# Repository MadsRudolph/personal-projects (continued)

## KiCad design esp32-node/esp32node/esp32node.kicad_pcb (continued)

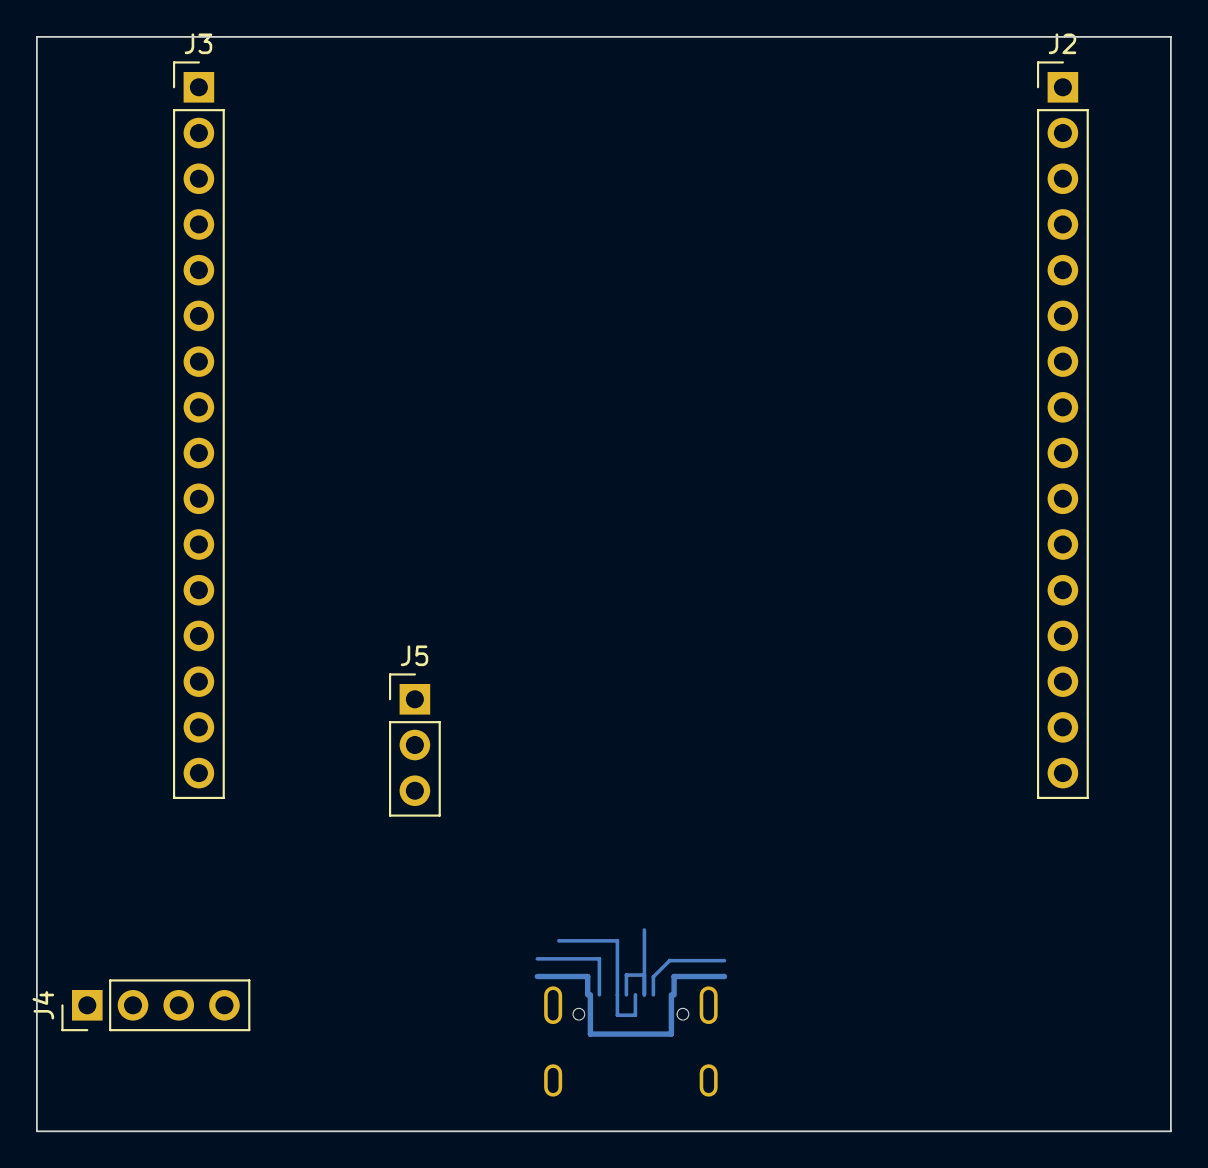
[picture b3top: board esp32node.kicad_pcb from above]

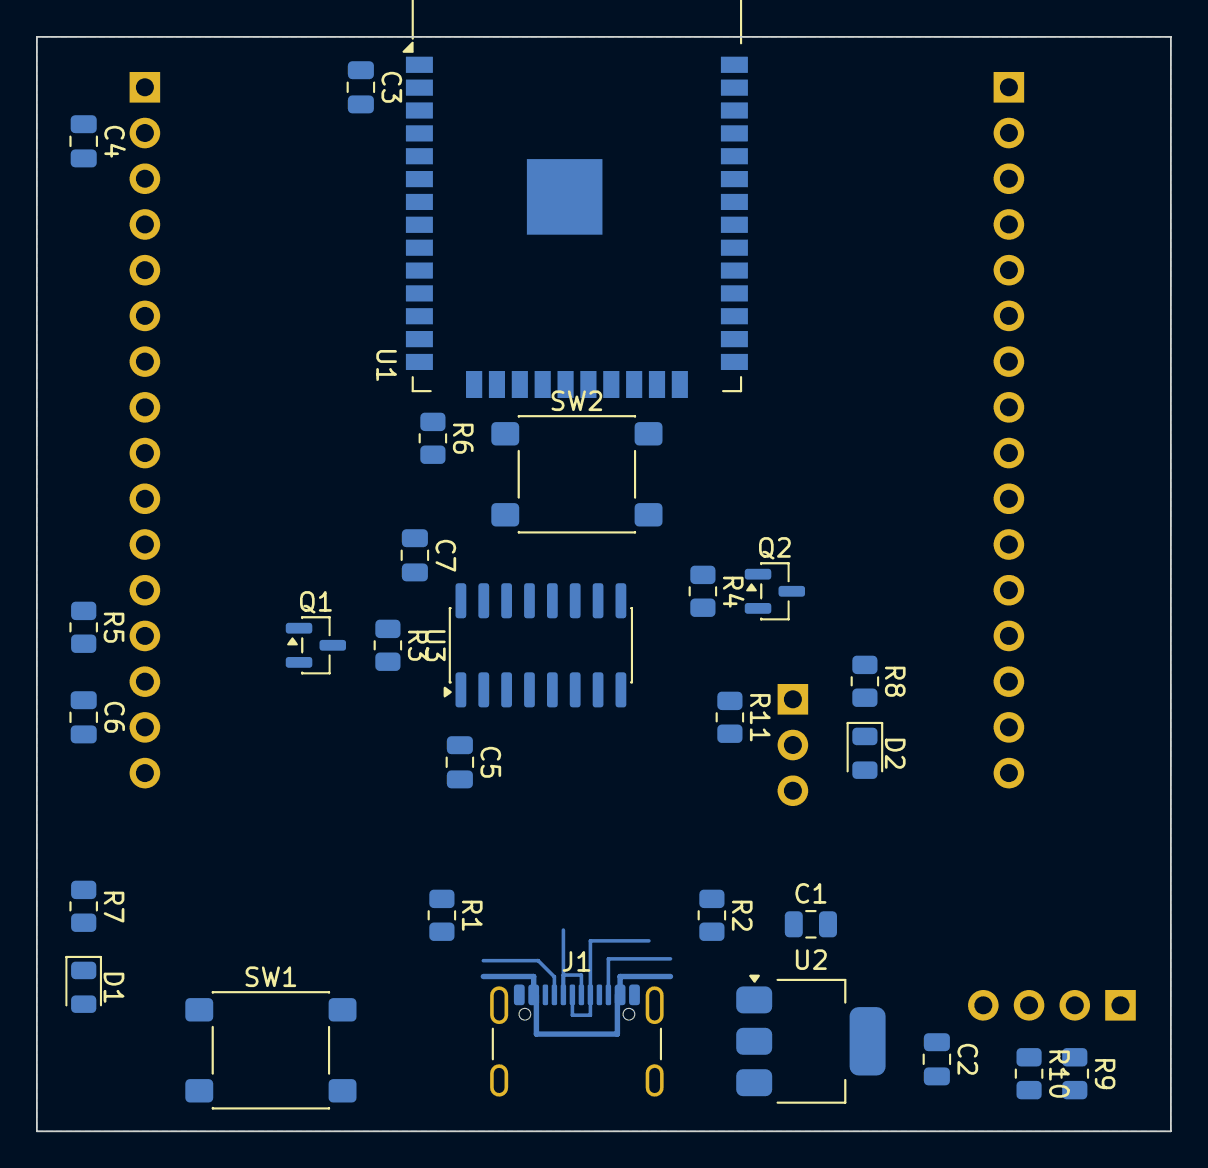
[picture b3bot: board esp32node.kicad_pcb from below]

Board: 2 copper layers, 63.0 x 60.8 mm, 32 parts (28 on the bottom side), 40 nets.

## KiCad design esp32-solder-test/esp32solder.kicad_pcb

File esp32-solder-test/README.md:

# ESP32 solder test board

This is the smallest board that proves an ESP32-WROOM-32 hand-soldered to copper etched on the
xTool F1 Ultra actually works. Once it's soldered, you flash it over a USB-UART adapter and blink the
LED on IO2. Everything except the module is through-hole and stocked at the DTU component shop.

- Single-sided, 54 x 46 mm, copper on the bottom (B.Cu). The ESP32 sits on the copper side and
  the through-hole parts go on top.
- Rule: 0.3 mm clearance / 0.5 mm track, inside what the test coupon proved (0.15 / 0.15 clean).
- Gates:
  - Schematic: `sch_score` PASS, ERC 0 violations, netlist verified.
  - Board: fully routed (11/11 nets, 0 unconnected, 0 vias, all tracks 0.5 mm), single GND pour
    in one piece, DRC clean on copper. The only leftovers are silkscreen cosmetics and one
    single-spoke thermal on SW2's GND pad, which is harmless.

## Bill of materials (DTU component shop part numbers)

| Ref | Part | Shop entry |
|---|---|---|
| U1 | ESP32-WROOM-32 module | not in the shop (bring your own) |
| U2 | LM317T, TO-220 | IC / Voltage Regulator / `LM317T` |
| R1 | 243 R | Resistor E96 `243R` |
| R2 | 392 R | Resistor E96 `392R` |
| R3, R4 | 10 k | Resistor E96 `10K0` |
| R5 | 332 R | Resistor E96 `332R` |
| R6 | 1 k | Resistor E96 `1K00` |
| C1, C2 | 10 uF electrolytic | Capacitor / Electrolytic `10µF` |
| C4 | 1 uF electrolytic | Capacitor / Electrolytic `1µF` |
| C3 | 100 nF ceramic | Capacitor / Ceramic `100n` |
| D1 | 3 mm LED, green (IO2) | LED `LED 3MM GRØN` |
| D2 | 3 mm LED, red (power) | LED `LED 3MM RØD` |
| SW1, SW2 | 6 mm tactile pushbutton | Hardware / Switch `Pushbutton` (check it has the 6.5 x 4.5 mm pin pattern) |
| J1 | 1x4 straight male header | Connector / Header `Header Male` (break off 4 pins) |

The shop has no fixed 3.3 V regulator, so the LM317 is set to 1.25 V x (1 + 392/243) = **3.27 V**.
R1 also draws the ~5 mA minimum load the LM317 needs. It needs about 1.7 V of headroom from 5 V,
which is plenty for flashing and blinking. WiFi does sag it: the factory AT firmware boot-looped
(see `BRINGUP.md`). The shop has no low-dropout 3.3 V part, so the fix for the next board is 7–9 V
into the LM317 plus 470 µF on 3V3. The recipe is in the kicad-laser-pcb skill's `references/esp32.md`.

## Laser files (`production/`)

Both files are **already mirrored to the copper side**, so do **not** mirror them in XCS.
Check: the copper text **"ESP32 TEST"** must read normally in the XCS preview.

1. **`esp32solder_copper_negative_MIRRORED.dxf`**: the copper to remove.
   - Import it, then **Make compound**. Black is removed; the pads, tracks and GND pour must be white.
   - Engrave with the **`Traces`** preset: 100 %, 600 mm/s, 10 passes, 240 lines/cm, one-way,
     30 kHz, cross hatch. See `../esp32-node/xtool/F1Ultra_PCB_presets.json`.
   - The drill holes are engraved as black dots in the pads, for centring.
2. **`esp32solder_drill_outline_MIRRORED.dxf`**: hole circles (layer `HOLES`) and board outline
   (layer `OUTLINE`).
   - Use the **`Cut/Drill`** vector preset (100 %, 100 mm/s, 160 passes). Both files share the
     same origin, so they stay registered if you import them into the same XCS canvas.
   - Hole sizes: 0.8 mm (resistors, caps), 0.9 mm (LEDs), 1.0 mm (header), 1.1 mm (LM317, buttons).

Sand lightly with 400 grit, then Framing, then Auto height adjustment, then Process.

## Soldering order

1. **ESP32 first**, while the board is still flat. It goes on the **copper side**, with the antenna
   overhanging the top edge, flush with the board edge. Tack two opposite corner pads, check
   alignment, then drag-solder the castellations. The big centre GND pad doesn't need solder;
   GND is carried by pins 1, 15 and 38.
2. Then the through-hole parts from the **plain side**, soldered on the copper side. Go lowest
   first: resistors, ceramic cap, LEDs (flat side = cathode), electrolytics (stripe = minus),
   buttons, header, and the LM317 last.
3. Before powering up, measure with a meter:
   - +5V to GND is not shorted.
   - Adjacent ESP32 pads are not bridged: probe neighbours, especially 1/2/3 (GND/3V3/EN) and
     34/35 (RXD0/TXD0).

## First power-up and flashing

- J1, starting at pin 1 (the square pad, nearest the antenna edge): **GND, 5V, TXD0 (ESP out), RXD0 (ESP in)**.
- Use a USB-UART adapter set to **3.3 V logic**. Wire adapter GND to GND, 5 V to 5V,
  adapter **RX to TXD0**, and adapter **TX to RXD0**.
- The red LED should light. Measure 3.2–3.3 V across C2.
- **Bootloader:** hold **BOOT**, tap **RESET**, release BOOT. Then run `esptool.py chip_id`
  (or `esptool.py flash_id`). If it answers, the module and all four UART/boot joints are good.
- Flash a blink sketch on **GPIO2** (Arduino `LED_BUILTIN` on the ESP32 Dev Module target) to see
  the green LED.

## Files

- `esp32solder_sch.py` builds `esp32solder.kicad_sch` (kicad-schematic DSL). It's the source of truth.
- `place_pcb.py` places the board (the footprint positions come from the flipped module's pads).
  The route came from FreeRouting 2.4.1 via `place_route.py`.
- `finish_pcb.py` adds the copper orientation text and refills the pour.
- `relink_pcb.py` links each footprint to its library and schematic symbol, so KiCad's
  schematic parity, cross-probing and "Update PCB from Schematic" work. `bootstrap_pcb.py`
  runs it automatically.
- `export_laser.py` writes the two DXFs above. It's the same negative-DXF approach as the coupon
  that came out perfectly.
- `esp32solder.placed.kicad_pcb` is the unrouted placement, kept for reference.
- `tools/pyshim` is a Python 3.14 workaround for pcbnew. Run the scripts with
  `PYTHONPATH=tools/pyshim python3 <script>`.

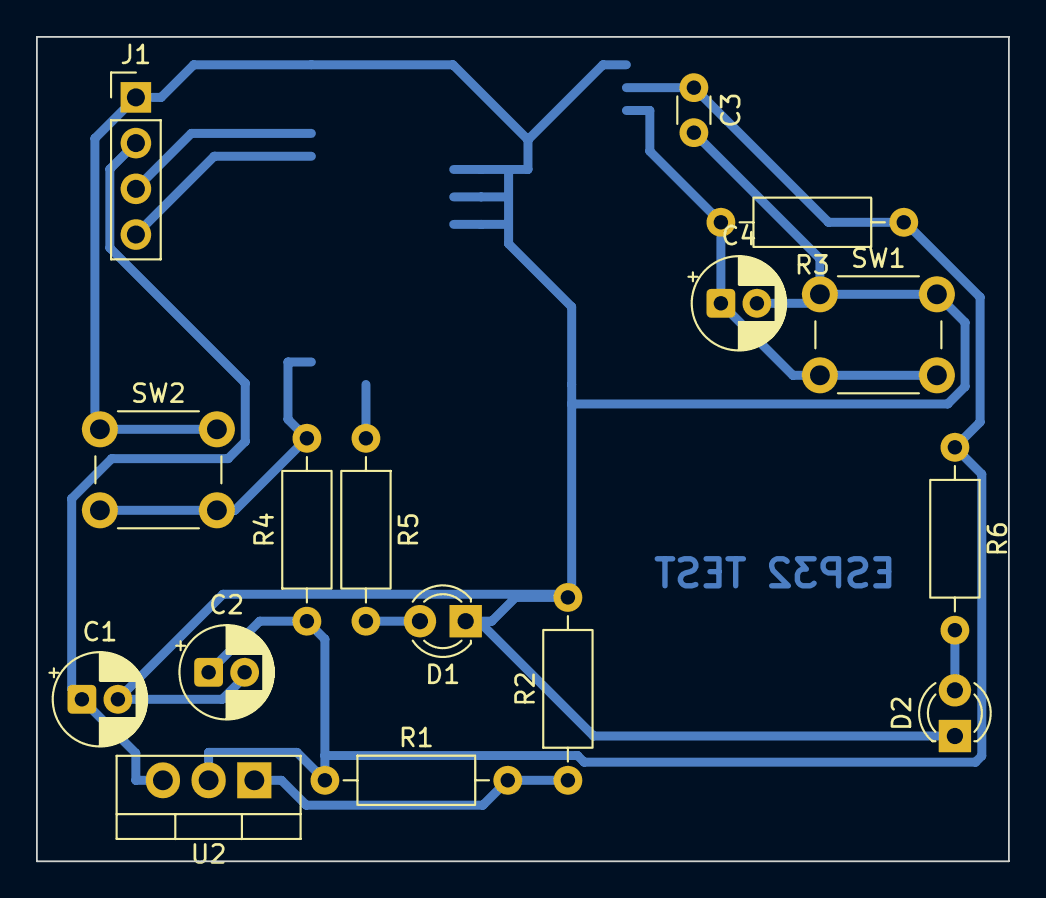
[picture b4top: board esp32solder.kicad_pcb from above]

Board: 2 copper layers, 54.0 x 45.8 mm, 17 parts (1 on the bottom side), 11 nets.

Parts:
C1, C2: 10u; CP_Radial_D5.0mm_P2.00mm
C3: 100n; C_Disc_D3.0mm_W1.6mm_P2.50mm
C4: 1u; CP_Radial_D5.0mm_P2.00mm
D1: LED green; LED_D3.0mm
D2: LED red; LED_D3.0mm
J1: UART / 5V; PinHeader_1x04_P2.54mm_Vertical
R1: 243; R_Axial_DIN0207_L6.3mm_D2.5mm_P10.16mm_Horizontal
R2: 392; R_Axial_DIN0207_L6.3mm_D2.5mm_P10.16mm_Horizontal
R3, R4: 10k; R_Axial_DIN0207_L6.3mm_D2.5mm_P10.16mm_Horizontal
R5: 332; R_Axial_DIN0207_L6.3mm_D2.5mm_P10.16mm_Horizontal
R6: 1k; R_Axial_DIN0207_L6.3mm_D2.5mm_P10.16mm_Horizontal
SW1: RESET; SW_PUSH_6mm
SW2: BOOT; SW_PUSH_6mm
U1: ESP32-WROOM-32; ESP32-WROOM-32_NoVias
U2: LM317T; TO-220-3_Vertical

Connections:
+3V3: C2.1, C3.1, R1.1, R3.1, R4.1, R6.1, U1.2, U2.2
/+5V_IN: C1.1, J1.2, U2.3
/IO0: R4.2, SW2.2, U1.25
/RXD0: J1.4, U1.34
/TXD0: J1.3, U1.35
GND: C1.2, C2.2, C3.2, C4.2, D1.1, D2.1, J1.1, R2.2, SW1.1, SW2.1, U1.1, U1.15, U1.38, U1.39
unnamed: D1.2, R5.2
unnamed: D2.2, R6.2
unnamed: C4.1, R3.2, SW1.2, U1.3
unnamed: R5.1, U1.24
unnamed: R1.2, R2.1, U2.1

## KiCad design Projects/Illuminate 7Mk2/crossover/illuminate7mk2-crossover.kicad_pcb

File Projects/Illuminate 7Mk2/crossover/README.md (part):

# Illuminate 7 Mk2 — crossover board

One passive crossover board per speaker, so **build two**. Single-sided,
through-hole only, CNC isolation-milled with an 0.8 mm end mill (the DTU 62768
process). The topology is the PrintYourSpeakers reference crossover, unchanged;
only the component **values** are substituted for what the DTU component shop
actually stocks.

| File | What it is |
|---|---|
| `illuminate7mk2-crossover.kicad_sch` / `.kicad_pro` | the schematic (KiCad 10) |
| `illuminate7mk2-crossover.pdf` / `.png` | rendered sheet |
| `illuminate7mk2-crossover-bom.csv` | BOM straight out of KiCad |
| `tools/crossover_layout.py` | the script that draws the sheet — edit this, not the `.kicad_sch` |
| `tools/make_coil_footprints.py` | generates the air-core coil footprints |
| `lib/crossover.pretty/` | those coil footprints |
| `sim/` | ngspice comparison of reference vs. substituted values |
| `illuminate7mk2-crossover.kicad_pcb` | the placed, unrouted board |
| `illuminate7mk2-crossover-pcb.png` | render of the placement |
| `tools/pcb_build.py` | builds and places the board from the netlist — re-run it after changing footprints |

Status: schematic done (ERC 0 violations), board routed by hand on B.Cu,
144.5 × 110 mm, four M4 corner holes, DRC clean. Mill and laser files are in
`production/illuminate7mk2-crossover/` (Gerbers + Excellon for the CAM,
`_silk_top.dxf` for the laser silkscreen). Coils: L102 may be a shop 270 µH if it passes
the LCR check; L101, L201 and L202 are to be wound.

## Circuit

```
IN+ ─┬─[ C 2u2 ∥ L 0.20mH ∥ R 9R4 ]─ A ─[ C 5u5 ]─ B ─[ C 10u1 ]─ TWEETER +
     │                                             └─[ L 0.25mH ]─┐
     │                                                            │
     └─[ C 41u ∥ L 0.70mH ∥ R 20R ]─ C ─[ L 2.0mH ]─ D ───────────┼─ WOOFER +
                                                    └─[ C 11u5 ]──┤
IN− ─────────────────────────────────────────────────────────────┴─ both −
```

The `GND` symbol on the sheet **is IN−**, the amplifier's negative speaker
terminal and the common return for both drivers. It is not chassis earth, and
the left and right boards' returns must stay separate — the Fosi V3 is a
bridged (BTL) class-D amp and its negative outputs are not ground.

## BOM

### From the DTU component shop — per board

| Qty | Shop part number | Refs | Replaces (design value) |
|----:|---|---|---|
| 2 | `2u2` film cap | C101, C103 | C101 = 2.0 µF tank; C103 is half of the 5.6 µF |
| 3 | `3u3` film cap | C102, C105, C207 | halves of 5.6 µF, 10 µF and 12 µF |
| 1 | `6u8` film cap | C104 | half of the 10 µF |
| 6 | `8u2` film cap | C201–C205, C206 | 5 in parallel = 40 µF tank; C206 is half of the 12 µF |
| 2 | `4R7 5W` power resistor | R101, R102 | in series = 9.4 Ω / 10 W (design 10 Ω) |
| 2 | `10R 5W` power resistor | R201, R202 | in series = 20 Ω / 10 W (design 20 Ω) |
| 3 | `2 pol skrueterminal` | J1, J2, J3 | input, tweeter, woofer |

**For two boards: double every quantity** — 4 × `2u2`, 6 × `3u3`, 2 × `6u8`,
12 × `8u2`, 4 × `4R7 5W`, 4 × `10R 5W`, 6 × 2-pole screw terminals.

How the parallel groups add up:

| Group | Shop parts | Result | Design value | Error |
|---|---|---|---|---|
| C101 | 2u2 | 2.2 µF | 2.0 µF | +10 % |
| C102 ∥ C103 | 3u3 + 2u2 | 5.5 µF | 5.6 µF | −1.8 % |
| C104 ∥ C105 | 6u8 + 3u3 | 10.1 µF | 10 µF | +1 % |
| C201…C205 | 5 × 8u2 | 41 µF | 40 µF | +2.5 % |
| C206 ∥ C207 | 8u2 + 3u3 | 11.5 µF | 12 µF | −4.2 % |
| R101 + R102 | 2 × 4R7 5W | 9.4 Ω / 10 W | 10 Ω / 10 W | −6 % |
| R201 + R202 | 2 × 10R 5W | 20 Ω / 10 W | 20 Ω / 10 W | exact |

### Coils — buy these, the shop has nothing usable

The shop stocks only small ferrite chokes with no current rating and a few bare
toroid cores, and no magnet wire. All four coils are **air-core, 0.8 mm
(20 AWG) wire**. Per board:

| Ref | Value | Target DCR | Dayton | Jantzen (Danish) |
|---|---|---|---|---|
| L101 | 0.20 mH | 0.29 Ω | AC20-20 | Air Core 0.20 mH / 0.80 mm |
| L102 | 0.25 mH | 0.35 Ω | AC20-25 | Air Core 0.25 mH / 0.80 mm |
| L201 | 0.70 mH | 0.60 Ω | AC20-70 | Air Core 0.70 mH / 0.80 mm |
| L202 | 2.0 mH | 1.06 Ω | AC202 | Air Core 2.0 mH / 0.80 mm |

Buy **eight** coils in total, two of each. Air-core only: an iron or ferrite
core saturates and distorts at woofer levels. Check the DCR on the datasheet —
it is part of the design, not a parasitic, and a coil with materially lower DCR
shifts the level of that branch.

### Or wind them yourself

Air-core coils are just wire on a bobbin, so with enamelled copper wire and an
LCR meter they can be wound at home. Use **0.8 mm** wire: it is what the Dayton
parts use, and it lands the DCR on the design value. Starting points (Wheeler
multilayer formula, 3D-printed bobbin, hand-wound with ~15 % slack):

| Ref | Value | Bobbin core Ø × width | Turns | Layers | OD | Wire | DCR |
|---|---|---|---|---|---|---|---|
| L101 | 0.20 mH | 20 × 10 mm | ~91 | 10 | ≈40 mm | 8.5 m | ≈0.29 Ω |
| L102 | 0.25 mH | 22 × 10 mm | ~96 | 10 | ≈42 mm | 9.6 m | ≈0.33 Ω |
| L201 | 0.70 mH | 28 × 12 mm | ~141 | 12 | ≈52 mm | 17.7 m | ≈0.60 Ω |
| L202 | 2.0 mH | 40 × 14 mm | ~195 | 14 | ≈68 mm | 33 m | ≈1.1 Ω |

Total wire for two boards: about 140 m of 0.8 mm. Procedure:

1. Print a bobbin with the core diameter above, flanges 2 mm taller than the
   expected winding depth, and a slot in one flange for the start lead.
2. Wind about 5 % fewer turns than the table, tight and in even layers, keeping
   the wire under tension. Count turns.
3. Measure L on the LCR meter at 1 kHz. Inductance goes with turns squared, so
   add turns as `N_new = N × sqrt(L_target / L_measured)`. Aim for ±3 %.
4. Measure DCR on the meter's DC-resistance range (or 4-wire if it has it) and
   compare with the target above. If the coil comes out *lower* than target,
   add a shop 5 W resistor in series to make up the difference (0.1–0.68 Ω are
   stocked); if it is more than ~0.1 Ω *higher*, the wire is thinner than
   0.8 mm or the coil is looser than assumed, and it is better to rewind.
5. Fix the winding with a few wraps of tape or a drop of glue, and keep the
   two coils of each branch at least one coil diameter apart, or at right
   angles, on the board so they do not couple.

Thicker wire (1.0 mm) gives about 30 % lower DCR than the design, so it needs
the series-resistor trim in step 4 on every coil; thinner wire (0.6 mm) makes
the DCR too high and should not be used for L202.

### Capacitor voltage ratings (read off the parts)

The Fosi V3 runs from 48 V and is bridged, so the input can swing about ±45 V.
The shop parts, as printed on them:

| Part | Rating | Verdict |
|---|---|---|
| 2u2 | 63 V | at the minimum; accepted, it is the weak point at full power |
| 3u3, 6u8 | 100 V | fine |
| 8u2 | 600 V | fine |

## Does this make an adequate crossover?

Yes. `sim/crossover_ac.cir` runs both versions side by side in ngspice with the
drivers modelled as plain resistors (4 Ω tweeter, 8 Ω woofer) and the coil DCRs
included, and `sim/compare.py` reports the difference over 100 Hz – 20 kHz:

| Branch | Max deviation from the reference | RMS |
|---|---|---|
| Tweeter | **+0.54 dB** at 12.7 kHz | 0.23 dB |
| Woofer | **+0.42 dB** at 1.05 kHz | 0.23 dB |

Nowhere in the band does either branch move more than 0.54 dB, and the woofer
stays under 0.5 dB everywhere. That is below the tolerance of the drivers
themselves (Dayton quotes ±10 % on Thiele-Small parameters, and 5 % film caps
are already worth a few tenths of a dB), and well under what is audible on a
broad, smooth deviation like this. The substituted set is fine.

Reproduce it with:

```bash
cd sim && ngspice -b crossover_ac.cir && python3 compare.py
```

## Board layout

`tools/pcb_build.py` builds the `.kicad_pcb` from the schematic netlist and
places it on a fixed floorplan that follows the signal flow, packed from the
footprints' real courtyards. **151 × 120 mm** on the measured
footprints, inside the mill's 203 × 152 mm envelope. Re-run after any footprint
change:

```bash
kicad-cli sch export netlist --format kicadsexpr -o /tmp/xo.net illuminate7mk2-crossover.kicad_sch
python3 ~/.claude/skills/kicad-laser-pcb/scripts/pcb_netlist_json.py /tmp/xo.net /tmp/xo.json
python3 tools/pcb_build.py /tmp/xo.json illuminate7mk2-crossover.kicad_pcb
```

```
 row A   L101 pads | C101 R101 R102 | C102 C103 | L102 pads | C104 C105 | J2 TWEETER   (top)
 row C   J1 IN, R201 R202 | C201 C202 C203 C204 C205 | L201 pads                     (middle)
 row B   L202 pads | C206 C207 | J3 WOOFER                                           (bottom)
```

- **The coils are not on the board.** They would not fit the mill envelope, so
  each coil has only its two lead pads (`crossover:L_OffBoard_P10.16mm`,
  10.16 mm pitch, 1.4 mm holes) at a board edge: L101 left edge top, L202 left
  edge bottom, L201 right edge middle, L102 top row between the tweeter caps.
  Mount the coil bodies overhanging the edge next to their pads, or glue them to
  the enclosure beside the board, and bring the leads to the pads. Keep any two
  coils at least one coil diameter apart, and never stack one on another.
- Input on the left edge, tweeter out top-right, woofer out bottom-right.
- Copper is **B.Cu only**, single-sided. A GND zone is defined on B.Cu (the
  return for both drivers) but not filled — fill it after routing.
- Design rules: 0.85 mm clearance, 1.0 mm minimum track, **2.0 mm default
  track**. Use 2 mm or wider for everything; this board carries amps.
- Four M4 holes in the corners, 6 mm in. The Illuminate enclosure has five M4
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
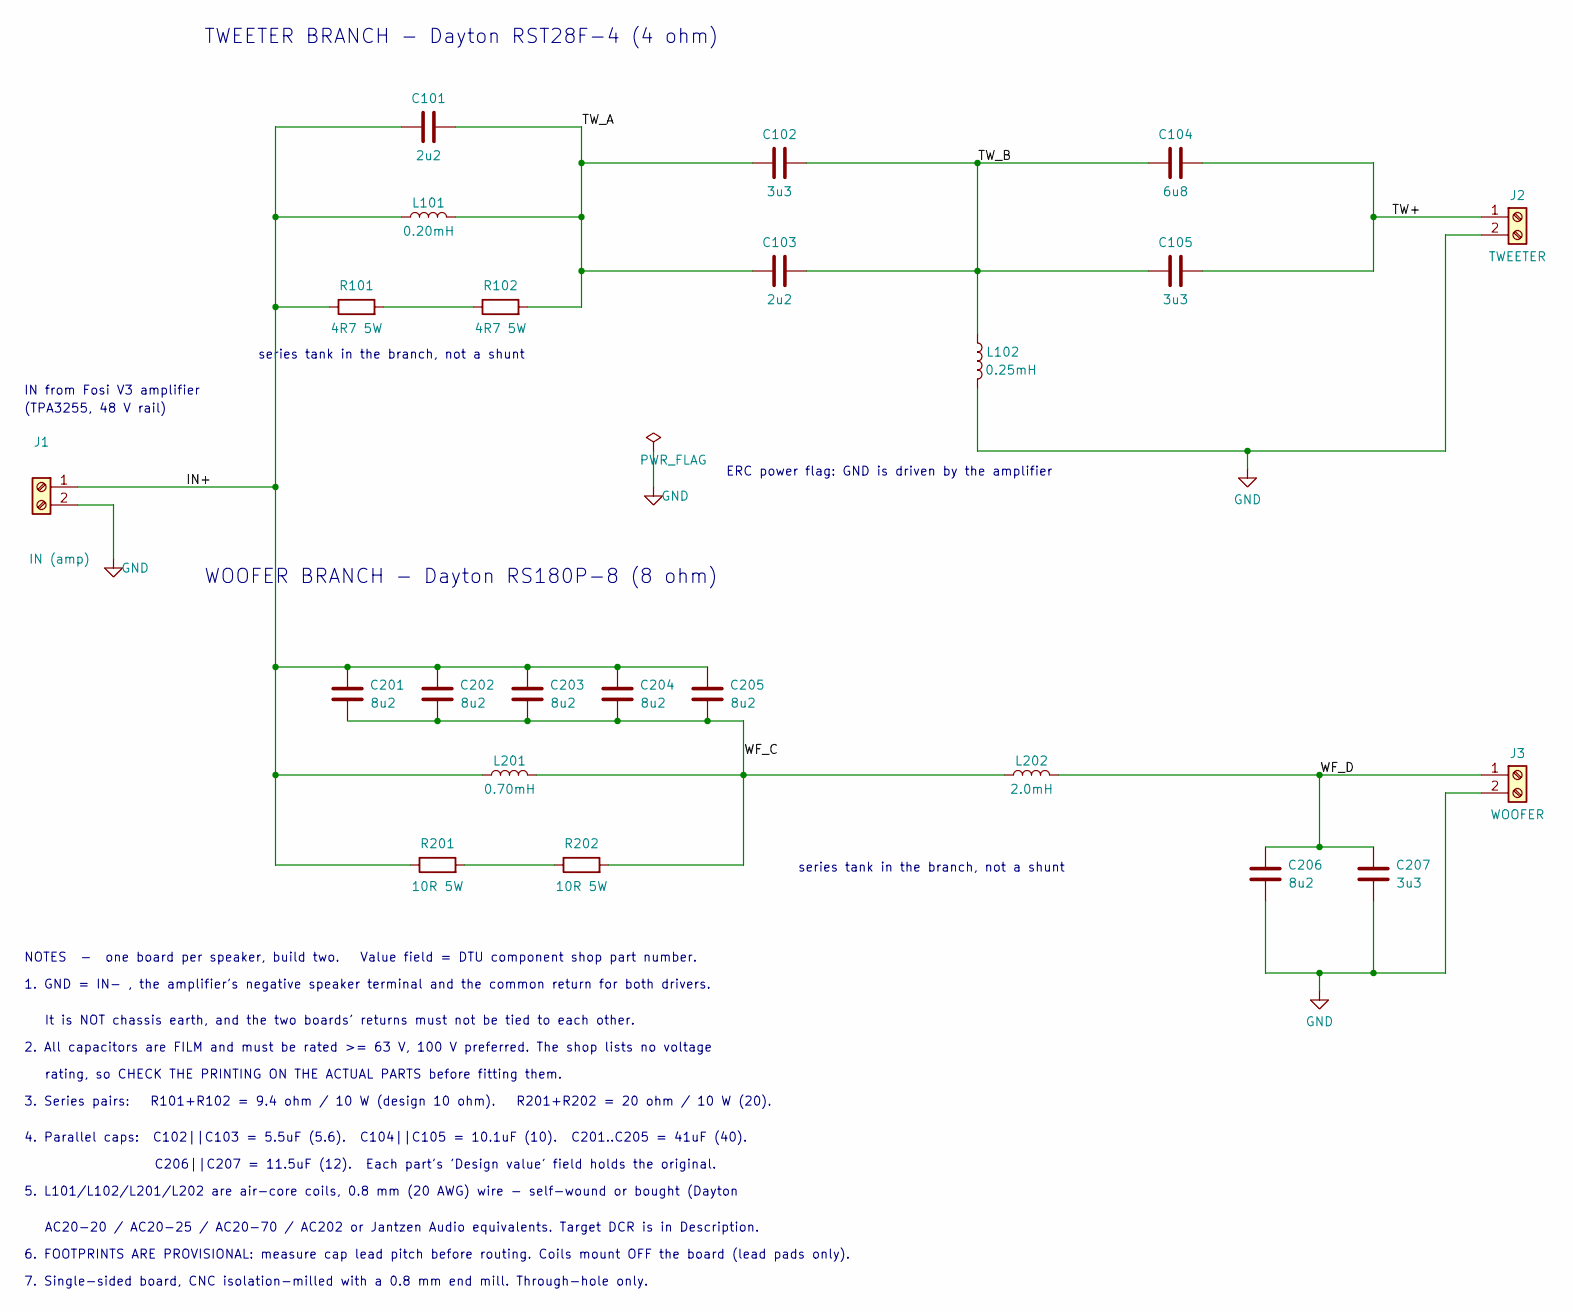
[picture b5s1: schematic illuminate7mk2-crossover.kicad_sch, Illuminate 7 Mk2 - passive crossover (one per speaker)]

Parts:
C101, C103: 2u2; C_Rect_L26.5mm_W7.0mm_P22.50mm_MKS4
C102, C105, C207: 3u3; C_Rect_L26.5mm_W8.5mm_P22.50mm_MKS4
C104: 6u8; C_Rect_L31.5mm_W11.0mm_P27.50mm_MKS4
C201, C202, C203, C204, C205, C206: 8u2; C_Rect_L31.5mm_W13.0mm_P27.50mm_MKS4
J1: IN (amp); TerminalBlock_MaiXu_MX126-5.0-02P_1x02_P5.00mm
J2: TWEETER; TerminalBlock_MaiXu_MX126-5.0-02P_1x02_P5.00mm
J3: WOOFER; TerminalBlock_MaiXu_MX126-5.0-02P_1x02_P5.00mm
L101: 0.20mH; L_OffBoard_P10.16mm
L102: 0.25mH; L_OffBoard_P10.16mm
L201: 0.70mH; L_OffBoard_P10.16mm
L202: 2.0mH; L_OffBoard_P10.16mm
R101, R102: 4R7 5W; R_Axial_Power_L25.0mm_W9.0mm_P27.94mm
R201, R202: 10R 5W; R_Axial_Power_L20.0mm_W6.4mm_P22.40mm

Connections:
/IN+: C101.1, C201.1, C202.1, C203.1, C204.1, C205.1, J1.1, L101.1, L201.1, R101.1, R201.1
/TW+: C104.2, C105.2, J2.1
/TW_A: C101.2, C102.1, C103.1, L101.2, R102.2
/TW_B: C102.2, C103.2, C104.1, C105.1, L102.1
/WF_C: C201.2, C202.2, C203.2, C204.2, C205.2, L201.2, L202.1, R202.2
/WF_D: C206.1, C207.1, J3.1, L202.2
GND: C206.2, C207.2, J1.2, J2.2, J3.2, L102.2
unnamed: R101.2, R102.1
unnamed: R201.2, R202.1

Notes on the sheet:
ERC power flag: GND is driven by the amplifier
TWEETER BRANCH - Dayton RST28F-4 (4 ohm)
WOOFER BRANCH - Dayton RS180P-8 (8 ohm)
IN from Fosi V3 amplifier
(TPA3255, 48 V rail)
series tank in the branch, not a shunt
NOTES - one board per speaker, build two. Value field = DTU component shop part number.
1. GND = IN- , the amplifier's negative speaker terminal and the common return for both drivers.
It is NOT chassis earth, and the two boards' returns must not be tied to each other.
2. All capacitors are FILM and must be rated >= 63 V, 100 V preferred. The shop lists no voltage
rating, so CHECK THE PRINTING ON THE ACTUAL PARTS before fitting them.
3. Series pairs: R101+R102 = 9.4 ohm / 10 W (design 10 ohm). R201+R202 = 20 ohm / 10 W (20).
4. Parallel caps: C102||C103 = 5.5uF (5.6). C104||C105 = 10.1uF (10). C201..C205 = 41uF (40).
C206||C207 = 11.5uF (12). Each part's 'Design value' field holds the original.
5. L101/L102/L201/L202 are air-core coils, 0.8 mm (20 AWG) wire - self-wound or bought (Dayton
AC20-20 / AC20-25 / AC20-70 / AC202 or Jantzen Audio equivalents. Target DCR is in Description.
6. FOOTPRINTS ARE PROVISIONAL: measure cap lead pitch before routing. Coils mount OFF the board (lead pads only).
7. Single-sided board, CNC isolation-milled with a 0.8 mm end mill. Through-hole only.

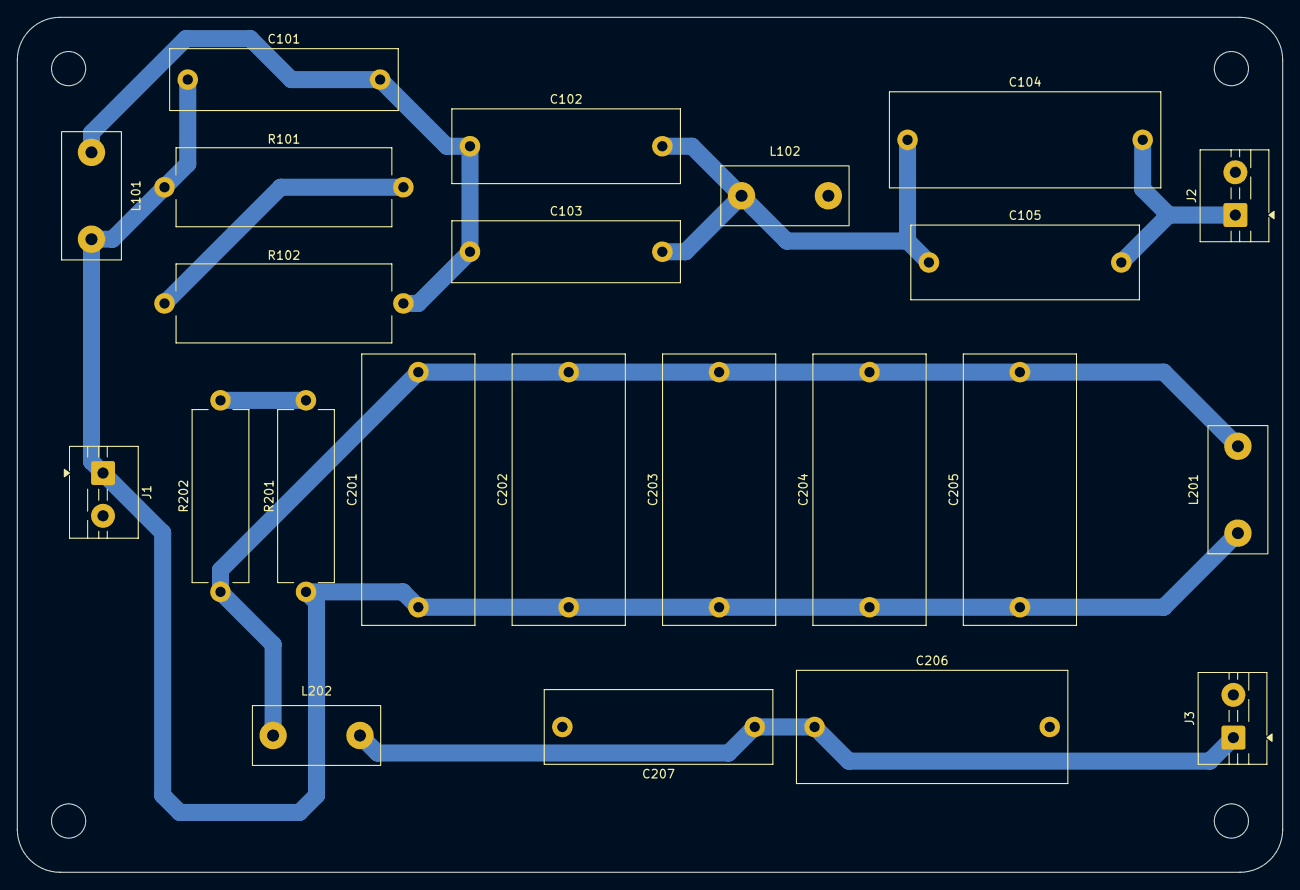
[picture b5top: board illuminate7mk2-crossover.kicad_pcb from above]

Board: 2 copper layers, 148.0 x 100.0 mm, 23 parts (0 on the bottom side), 9 nets.

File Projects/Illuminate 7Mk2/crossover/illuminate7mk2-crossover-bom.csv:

"Reference","Value","Design value","Description","Footprint"
"C101","2u2","2.0 uF","Tank cap, tweeter notch","Capacitor_THT:C_Rect_L26.5mm_W7.0mm_P22.50mm_MKS4"
"C102","3u3","5.6 uF (half)","C102 || C103 = 5.5 uF series cap","Capacitor_THT:C_Rect_L26.5mm_W8.5mm_P22.50mm_MKS4"
"C103","2u2","5.6 uF (half)","C102 || C103 = 5.5 uF series cap","Capacitor_THT:C_Rect_L26.5mm_W7.0mm_P22.50mm_MKS4"
"C104","6u8","10 uF (half)","C104 || C105 = 10.1 uF series cap","Capacitor_THT:C_Rect_L31.5mm_W11.0mm_P27.50mm_MKS4"
"C105","3u3","10 uF (half)","C104 || C105 = 10.1 uF series cap","Capacitor_THT:C_Rect_L26.5mm_W8.5mm_P22.50mm_MKS4"
"C201","8u2","40 uF (fifth)","C201..C205 in parallel = 41 uF tank cap","Capacitor_THT:C_Rect_L31.5mm_W13.0mm_P27.50mm_MKS4"
"C202","8u2","40 uF (fifth)","C201..C205 in parallel = 41 uF tank cap","Capacitor_THT:C_Rect_L31.5mm_W13.0mm_P27.50mm_MKS4"
"C203","8u2","40 uF (fifth)","C201..C205 in parallel = 41 uF tank cap","Capacitor_THT:C_Rect_L31.5mm_W13.0mm_P27.50mm_MKS4"
"C204","8u2","40 uF (fifth)","C201..C205 in parallel = 41 uF tank cap","Capacitor_THT:C_Rect_L31.5mm_W13.0mm_P27.50mm_MKS4"
"C205","8u2","40 uF (fifth)","C201..C205 in parallel = 41 uF tank cap","Capacitor_THT:C_Rect_L31.5mm_W13.0mm_P27.50mm_MKS4"
"C206","8u2","12 uF (half)","C206 || C207 = 11.5 uF shunt cap","Capacitor_THT:C_Rect_L31.5mm_W13.0mm_P27.50mm_MKS4"
"C207","3u3","12 uF (half)","C206 || C207 = 11.5 uF shunt cap","Capacitor_THT:C_Rect_L26.5mm_W8.5mm_P22.50mm_MKS4"
"J1","IN (amp)","","From Fosi V3 speaker output. Pin1 = IN+, Pin2 = IN- (common)","TerminalBlock:TerminalBlock_MaiXu_MX126-5.0-02P_1x02_P5.00mm"
"J2","TWEETER","","Dayton RST28F-4, 4 ohm. Pin1 = +, Pin2 = -","TerminalBlock:TerminalBlock_MaiXu_MX126-5.0-02P_1x02_P5.00mm"
"J3","WOOFER","","Dayton RS180P-8, 8 ohm. Pin1 = +, Pin2 = -","TerminalBlock:TerminalBlock_MaiXu_MX126-5.0-02P_1x02_P5.00mm"
"L101","0.20mH","200 uH","Air core 0.8 mm wire, target DCR 0.29 ohm","crossover:L_OffBoard_P10.16mm"
"L102","0.25mH","250 uH","Air core 0.8 mm wire, target DCR 0.35 ohm","crossover:L_OffBoard_P10.16mm"
"L201","0.70mH","700 uH","Air core 0.8 mm wire, target DCR 0.60 ohm","crossover:L_OffBoard_P10.16mm"
"L202","2.0mH","2.0 mH","Air core 0.8 mm wire, target DCR 1.06 ohm","crossover:L_OffBoard_P10.16mm"
"R101","4R7 5W","10 ohm 10 W (half)","R101+R102 in series = 9.4 ohm / 10 W","Resistor_THT:R_Axial_Power_L25.0mm_W9.0mm_P27.94mm"
"R102","4R7 5W","10 ohm 10 W (half)","R101+R102 in series = 9.4 ohm / 10 W","Resistor_THT:R_Axial_Power_L25.0mm_W9.0mm_P27.94mm"
"R201","10R 5W","20 ohm 10 W (half)","R201+R202 in series = 20 ohm / 10 W","Resistor_THT:R_Axial_Power_L20.0mm_W6.4mm_P22.40mm"
"R202","10R 5W","20 ohm 10 W (half)","R201+R202 in series = 20 ohm / 10 W","Resistor_THT:R_Axial_Power_L20.0mm_W6.4mm_P22.40mm"

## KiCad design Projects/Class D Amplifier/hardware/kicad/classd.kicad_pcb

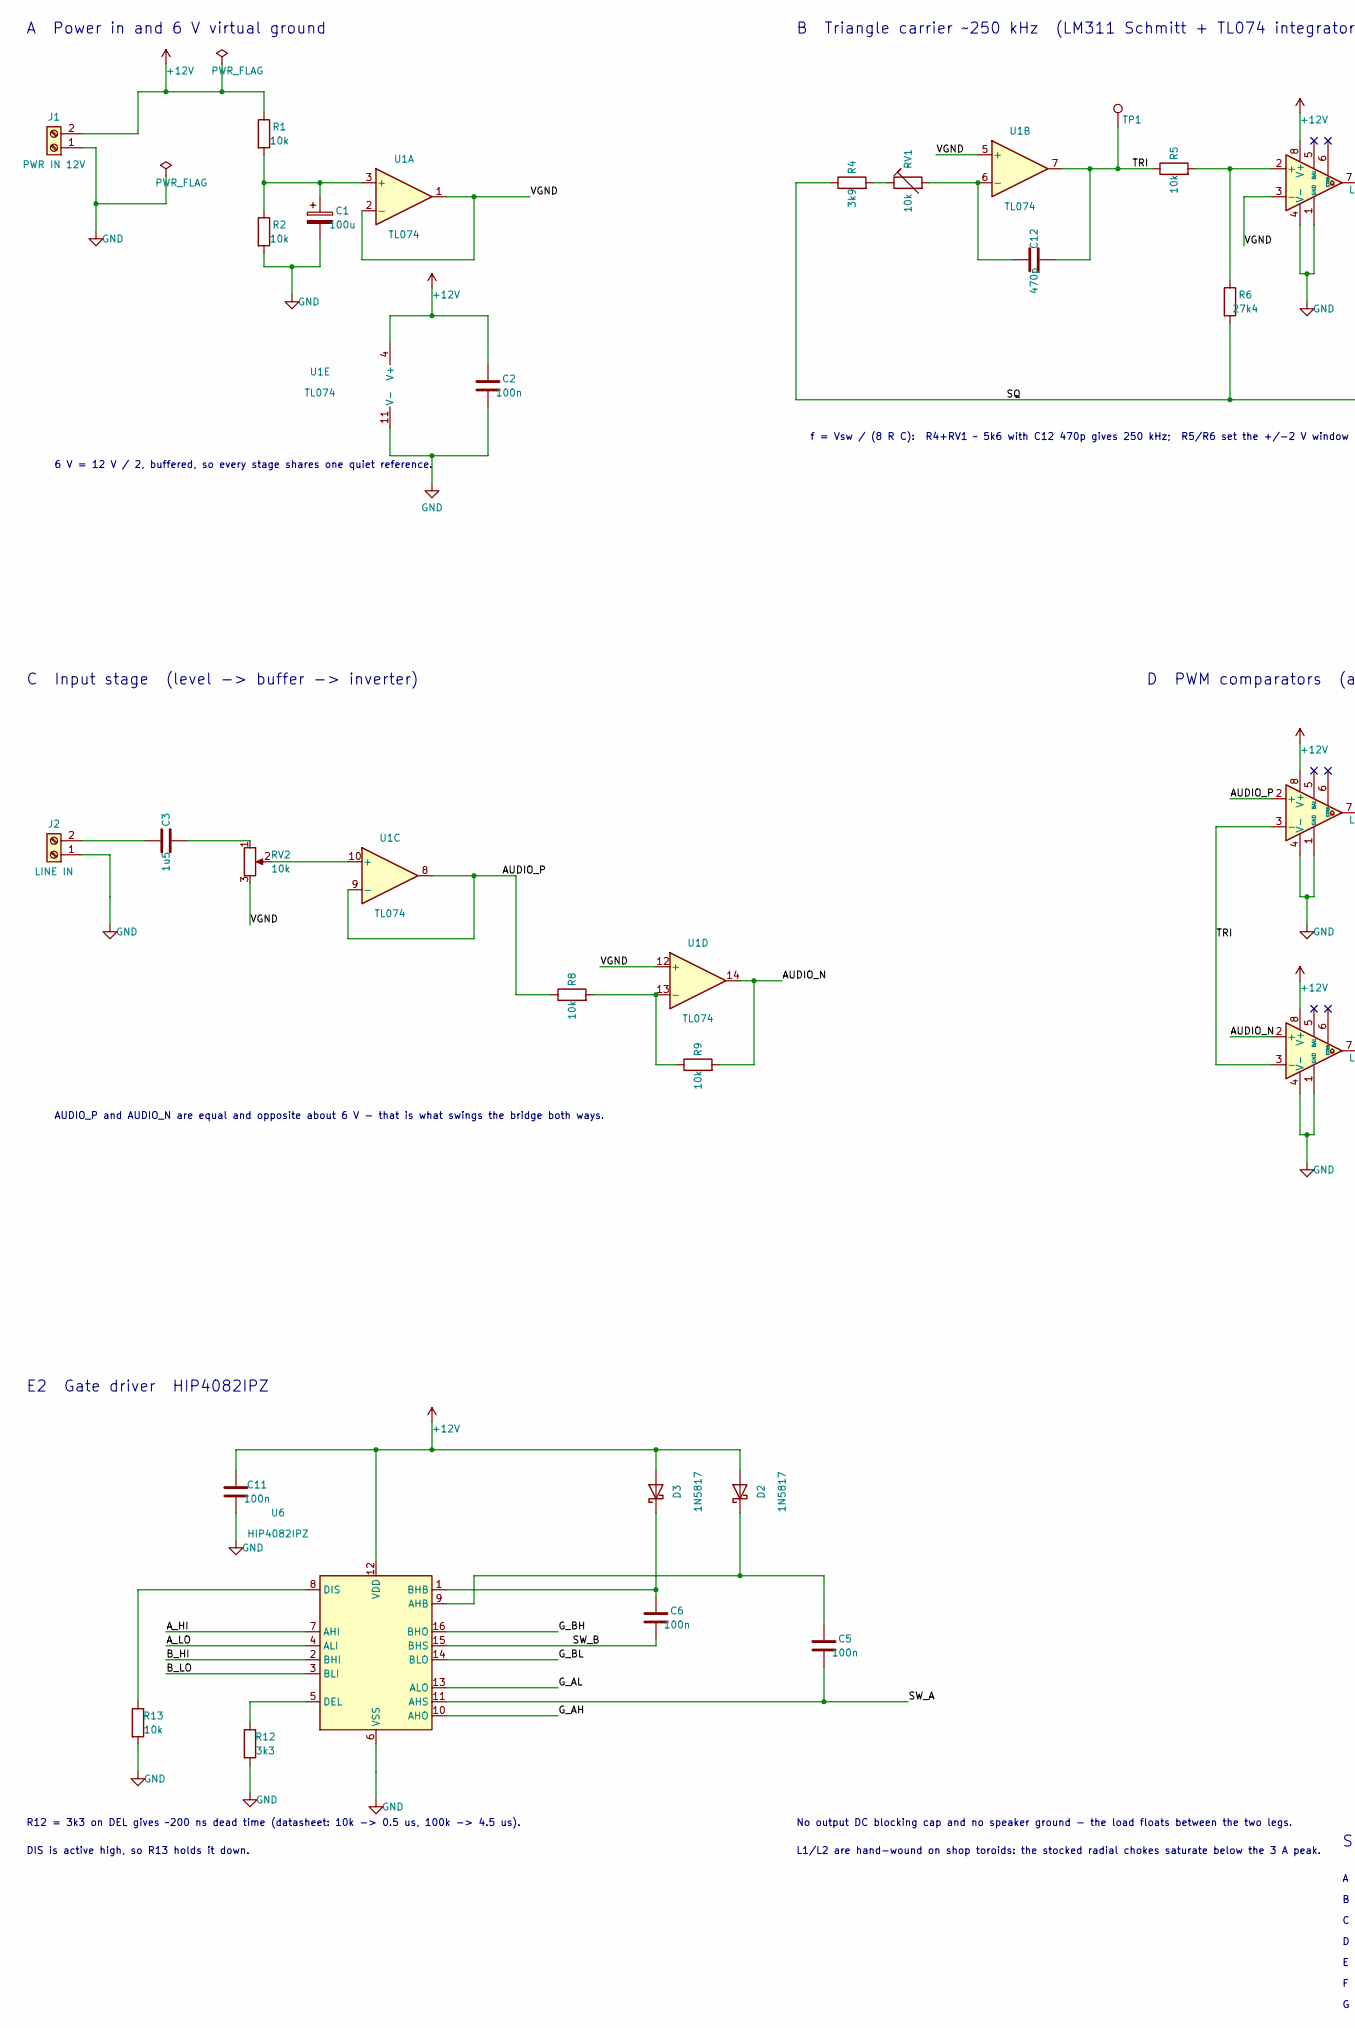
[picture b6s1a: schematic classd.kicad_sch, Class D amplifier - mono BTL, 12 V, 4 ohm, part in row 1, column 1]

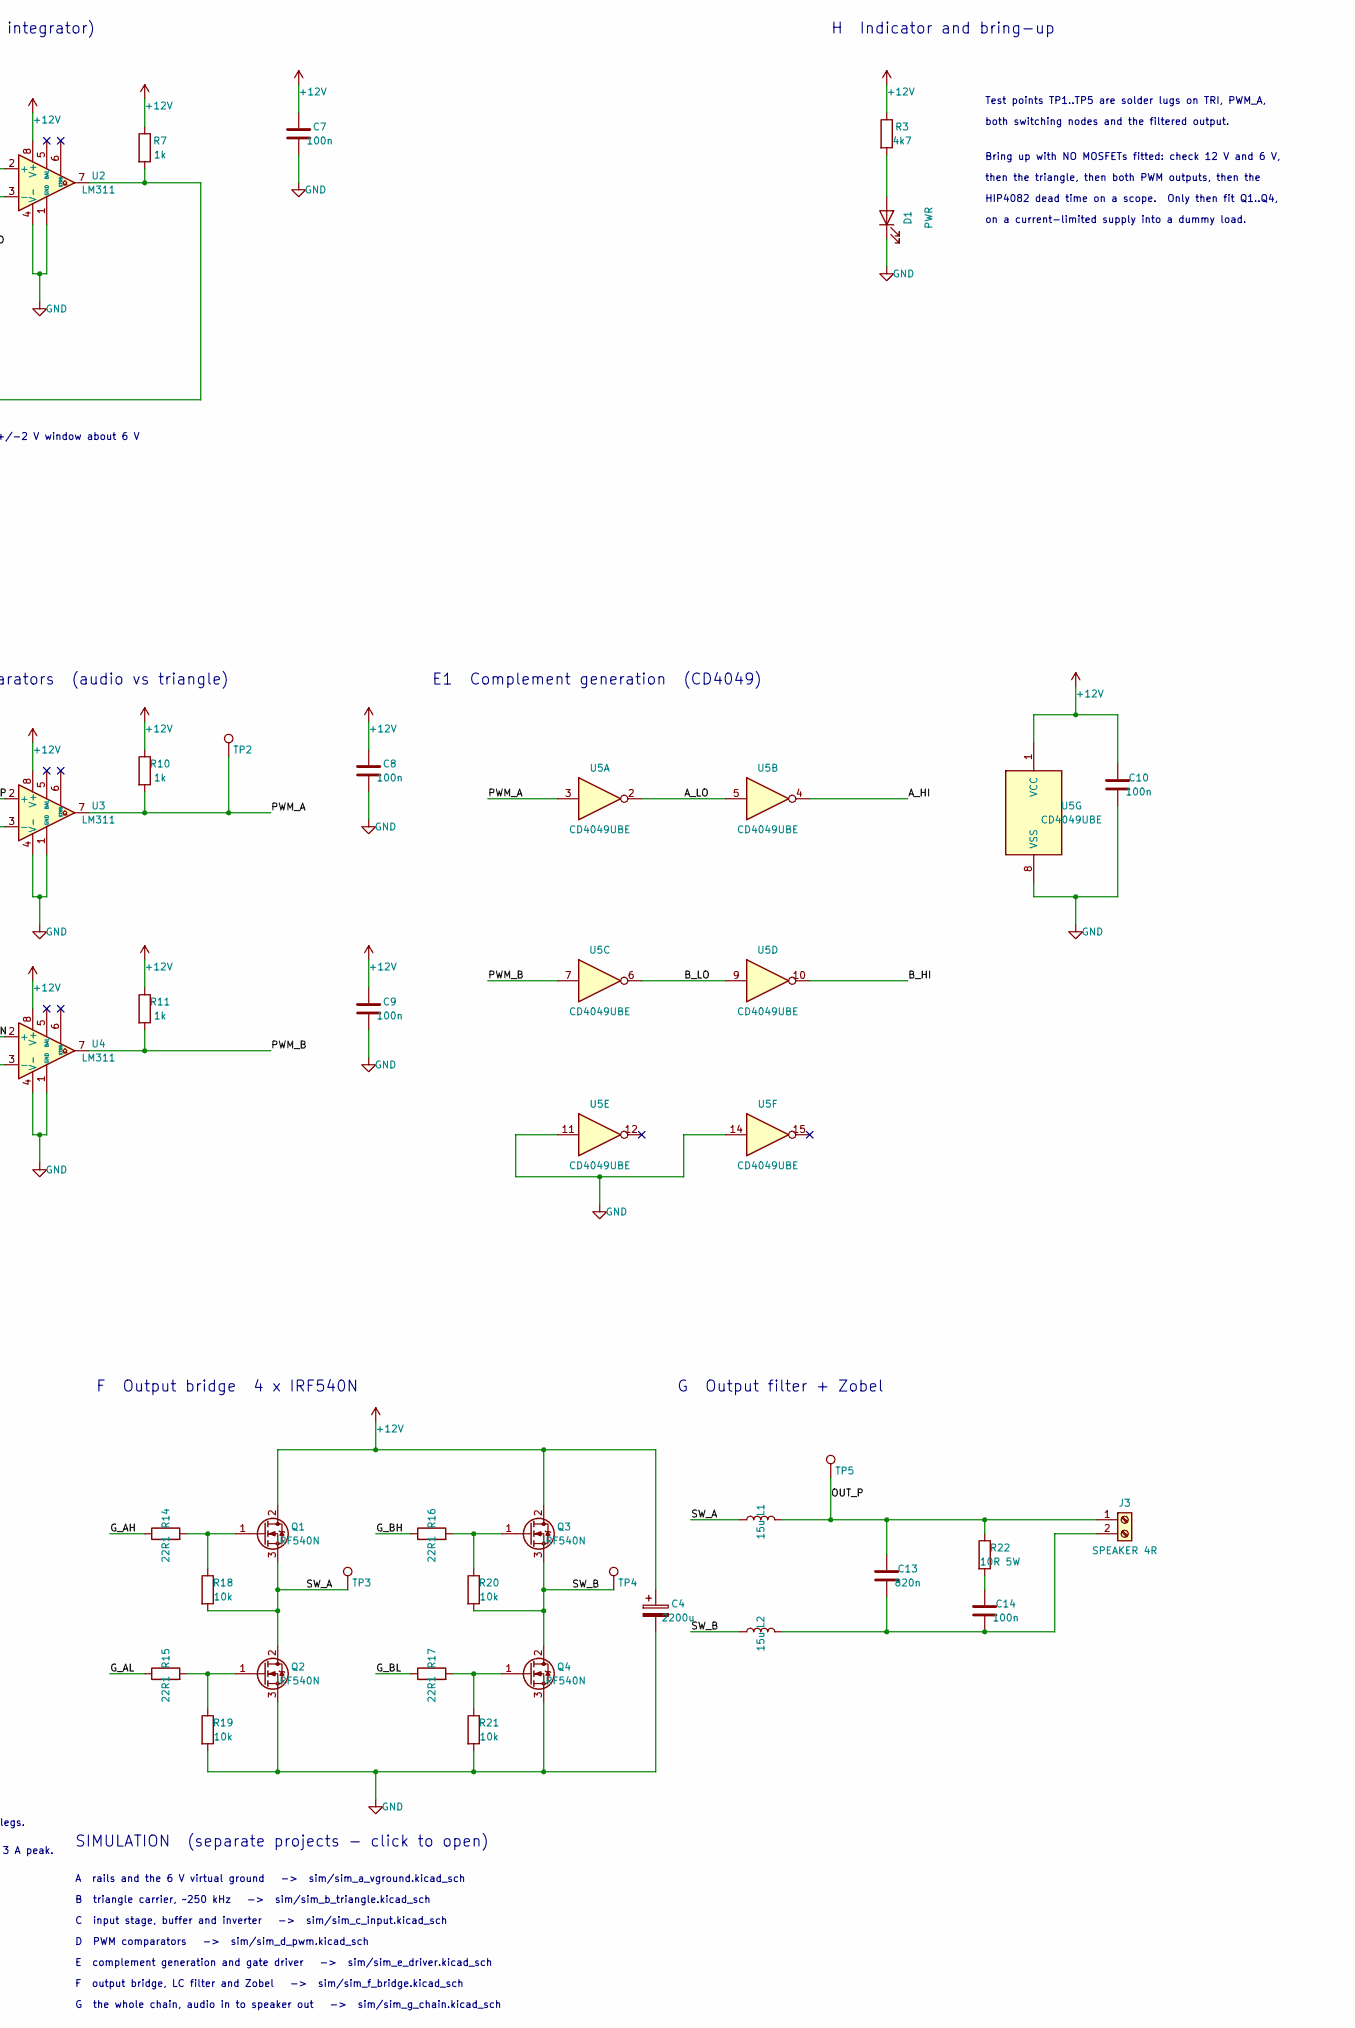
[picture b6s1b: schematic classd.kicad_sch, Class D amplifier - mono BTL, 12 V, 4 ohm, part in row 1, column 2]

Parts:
C1: 100u; CP_Radial_D8.0mm_P3.50mm
C2, C5, C6, C7, C8, C9, C10, C11: 100n; C_Disc_D5.0mm_W2.5mm_P5.00mm
C3: 1u5; C_Rect_L13.0mm_W5.0mm_P10.00mm_FKS3_FKP3_MKS4
C4: 2200u; CP_Radial_D18.0mm_P7.50mm
C12: 470p; C_Disc_D5.0mm_W2.5mm_P5.00mm
C13: 820n; C_Rect_L16.5mm_W5.0mm_P15.00mm_MKT
C14: 100n; C_Rect_L7.0mm_W3.5mm_P5.00mm
D1: PWR; LED_D3.0mm_P5.08mm_LaserPads
D2, D3: 1N5817; D_DO-41_SOD81_P10.16mm_Horizontal
J1: PWR IN 12V; TerminalBlock_bornier-2_P5.08mm
J2: LINE IN; TerminalBlock_bornier-2_P5.08mm
J3: SPEAKER 4R; TerminalBlock_bornier-2_P5.08mm
L1, L2: 15u; L_Toroid_Vertical_L34.5mm_W15.0mm_P28.20mm_LaserPads
Q1, Q2, Q3, Q4: IRF540N; TO-220-3_Vertical_LaserPads
R1, R2, R5, R8, R9, R13, R18, R19, R20, R21: 10k; R_Axial_DIN0207_L6.3mm_D2.5mm_P7.62mm_Horizontal
R3: 4k7; R_Axial_DIN0207_L6.3mm_D2.5mm_P7.62mm_Horizontal
R4: 3k9; R_Axial_DIN0207_L6.3mm_D2.5mm_P7.62mm_Horizontal
R6: 27k4; R_Axial_DIN0207_L6.3mm_D2.5mm_P7.62mm_Horizontal
R7, R10, R11: 1k; R_Axial_DIN0207_L6.3mm_D2.5mm_P7.62mm_Horizontal
R12: 3k3; R_Axial_DIN0207_L6.3mm_D2.5mm_P7.62mm_Horizontal
R14, R15, R16, R17: 22R1; R_Axial_DIN0207_L6.3mm_D2.5mm_P7.62mm_Horizontal
R22: 10R 5W; R_Axial_Power_L25.0mm_W9.0mm_P30.48mm
RV1: 10k; Potentiometer_Bourns_3296W_Vertical
RV2: 10k; Potentiometer_ACP_CA14V-15_Vertical
TP1, TP2, TP3, TP4, TP5: TestPoint_THTPad_2.5x2.5mm_Drill1.2mm
U1: TL074; DIP-14_W7.62mm_LongPads
U2, U3, U4: LM311; DIP-8_W7.62mm_LongPads
U5: CD4049UBE; DIP-16_W7.62mm_LongPads
U6: HIP4082IPZ; DIP-16_W7.62mm_LongPads

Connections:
/AUDIO_N: R9.2, U1.14, U4.2 (+)
/AUDIO_P: R8.1, U1.8, U1.9 (-), U3.2 (+)
/A_HI: U5.4, U6.7 (AHI)
/A_LO: U5.2, U5.5, U6.4 (ALI)
/B_HI: U5.10, U6.2 (BHI)
/B_LO: U5.6, U5.9, U6.3 (BLI)
/G_AH: R14.1, U6.10 (AHO)
/G_AL: R15.1, U6.13 (ALO)
/G_BH: R16.1, U6.16 (BHO)
/G_BL: R17.1, U6.14 (BLO)
/OUT_P: C13.1, J3.1, L1.2, R22.1, TP5.1 (1_1)
/PWM_A: R10.2, TP2.1 (1_1), U3.7, U5.3
/PWM_B: R11.2, U4.7, U5.7
/SQ: R4.1, R6.2, R7.2, U2.7
/SW_A: C5.2, L1.1, Q1.3 (S), Q2.2 (D), R18.2, TP3.1 (1_1), U6.11 (AHS)
/SW_B: C6.2, L2.1, Q3.3 (S), Q4.2 (D), R20.2, TP4.1 (1_1), U6.15 (BHS)
/TRI: C12.2, R5.1, TP1.1 (1_1), U1.7, U3.3 (-), U4.3 (-)
/VGND: RV2.3, U1.1, U1.2 (-), U1.5 (+), U1.12 (+), U2.3 (-)
unnamed: C3.2, RV2.1
unnamed: C14.1, R22.2
unnamed: D1.2 (A), R3.2
unnamed: C5.1, D2.1 (K), U6.9 (AHB)
unnamed: C6.1, D3.1 (K), U6.1 (BHB)
unnamed: C3.1, J2.2
unnamed: C13.2, C14.2, J3.2, L2.2
unnamed: Q1.1 (G), R14.2, R18.1
unnamed: Q2.1 (G), R15.2, R19.1
unnamed: Q3.1 (G), R16.2, R20.1
unnamed: Q4.1 (G), R17.2, R21.1
unnamed: R4.2, RV1.1
unnamed: C1.1, R1.2, R2.1, U1.3 (+)
unnamed: C12.1, RV1.2, U1.6 (-)
unnamed: RV2.2, U1.10 (+)
unnamed: R8.2, R9.1, U1.13 (-)
unnamed: R5.2, R6.1, U2.2 (+)
unnamed: R12.1, U6.5 (DEL)
unnamed: R13.1, U6.8 (DIS)

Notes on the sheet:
A Power in and 6 V virtual ground
6 V = 12 V / 2, buffered, so every stage shares one quiet reference.
B Triangle carrier ~250 kHz (LM311 Schmitt + TL074 integrator)
f = Vsw / (8 R C): R4+RV1 ~ 5k6 with C12 470p gives 250 kHz; R5/R6 set the +/-2 V window about 6 V
H Indicator and bring-up
Test points TP1..TP5 are solder lugs on TRI, PWM_A,
both switching nodes and the filtered output.
Bring up with NO MOSFETs fitted: check 12 V and 6 V,
then the triangle, then both PWM outputs, then the
HIP4082 dead time on a scope. Only then fit Q1..Q4,
on a current-limited supply into a dummy load.
C Input stage (level -> buffer -> inverter)
AUDIO_P and AUDIO_N are equal and opposite about 6 V - that is what swings the bridge both ways.
D PWM comparators (audio vs triangle)
E1 Complement generation (CD4049)
E2 Gate driver HIP4082IPZ
R12 = 3k3 on DEL gives ~200 ns dead time (datasheet: 10k -> 0.5 us, 100k -> 4.5 us).
DIS is active high, so R13 holds it down.
F Output bridge 4 x IRF540N
G Output filter + Zobel
No output DC blocking cap and no speaker ground - the load floats between the two legs.
L1/L2 are hand-wound on shop toroids: the stocked radial chokes saturate below the 3 A peak.
SIMULATION (separate projects - click to open)
A rails and the 6 V virtual ground -> sim/sim_a_vground.kicad_sch
B triangle carrier, ~250 kHz -> sim/sim_b_triangle.kicad_sch
C input stage, buffer and inverter -> sim/sim_c_input.kicad_sch
D PWM comparators -> sim/sim_d_pwm.kicad_sch
E complement generation and gate driver -> sim/sim_e_driver.kicad_sch
F output bridge, LC filter and Zobel -> sim/sim_f_bridge.kicad_sch
G the whole chain, audio in to speaker out -> sim/sim_g_chain.kicad_sch

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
